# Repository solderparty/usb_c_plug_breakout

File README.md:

# USB Type-C Plug Breakout Boards

Two breakout boards for a USB Type-C Plug connector. One with USB 2.0 pins only and one with USB 3.0.

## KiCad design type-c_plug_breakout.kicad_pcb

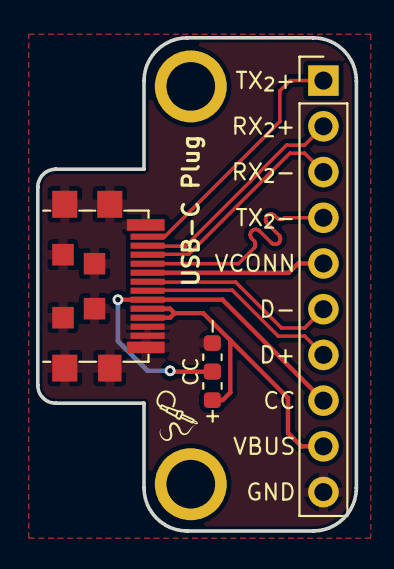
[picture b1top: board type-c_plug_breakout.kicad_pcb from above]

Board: 2 copper layers, 17.7 x 27.4 mm, 4 parts (0 on the bottom side), 10 nets.

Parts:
J1: Conn_01x10; PinHeader_1x10_P2.54mm_Vertical
P1: USB_C_Plug; USB_C_Plug_UTC009-C12
R1: PullUp; R_0603_1608Metric
R2: PullDown; R_0603_1608Metric

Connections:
/CC: J1.8, P1.A5 (CC), R1.2, R2.1
/D+: J1.7, P1.A6 (D+)
/D-: J1.6, P1.A7 (D-)
/RX2+: J1.2, P1.A11 (RX2+)
/RX2-: J1.3, P1.A10 (RX2-)
/TX2+: J1.1, P1.B2 (TX2+)
/TX2-: J1.4, P1.B3 (TX2-)
/VCONN: J1.5, P1.B5 (VCONN)
GND: J1.10, P1.A1 (GND), P1.B12 (GND), P1.S1 (SHIELD), R2.2
VBUS: J1.9, P1.A4 (VBUS), P1.B9 (VBUS), R1.1

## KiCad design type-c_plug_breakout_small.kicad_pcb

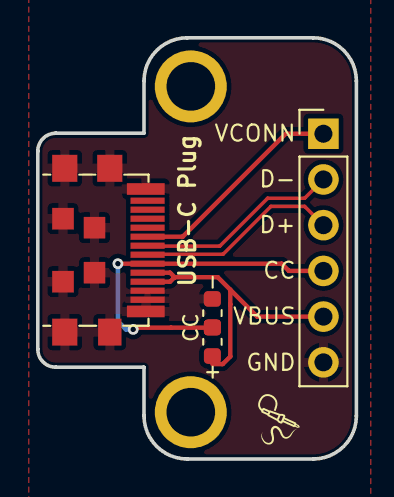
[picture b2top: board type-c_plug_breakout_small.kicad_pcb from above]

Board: 2 copper layers, 17.7 x 23.4 mm, 4 parts (0 on the bottom side), 6 nets.

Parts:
J1: Conn_01x06; PinHeader_1x06_P2.54mm_Vertical
P1: USB_C_Plug; USB_C_Plug_UTC009-C12
R1: PullUp; R_0603_1608Metric
R2: PullDown; R_0603_1608Metric

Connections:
/CC: J1.4, P1.A5 (CC), R1.2, R2.1
/D+: J1.3, P1.A6 (D+)
/D-: J1.2, P1.A7 (D-)
/VCONN: J1.1, P1.B5 (VCONN)
GND: J1.6, P1.A1 (GND), P1.B12 (GND), P1.S1 (SHIELD), R2.2
VBUS: J1.5, P1.A4 (VBUS), P1.B9 (VBUS), R1.1

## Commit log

2020-12-14 Initial import
